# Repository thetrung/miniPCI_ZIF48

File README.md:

mini-PCI to ZIF-48P
====================
Just a simple PCB Design practice to make old mini-pcie-type-3 with single-side 62 pins to connect to socket ZIF-48 pins.

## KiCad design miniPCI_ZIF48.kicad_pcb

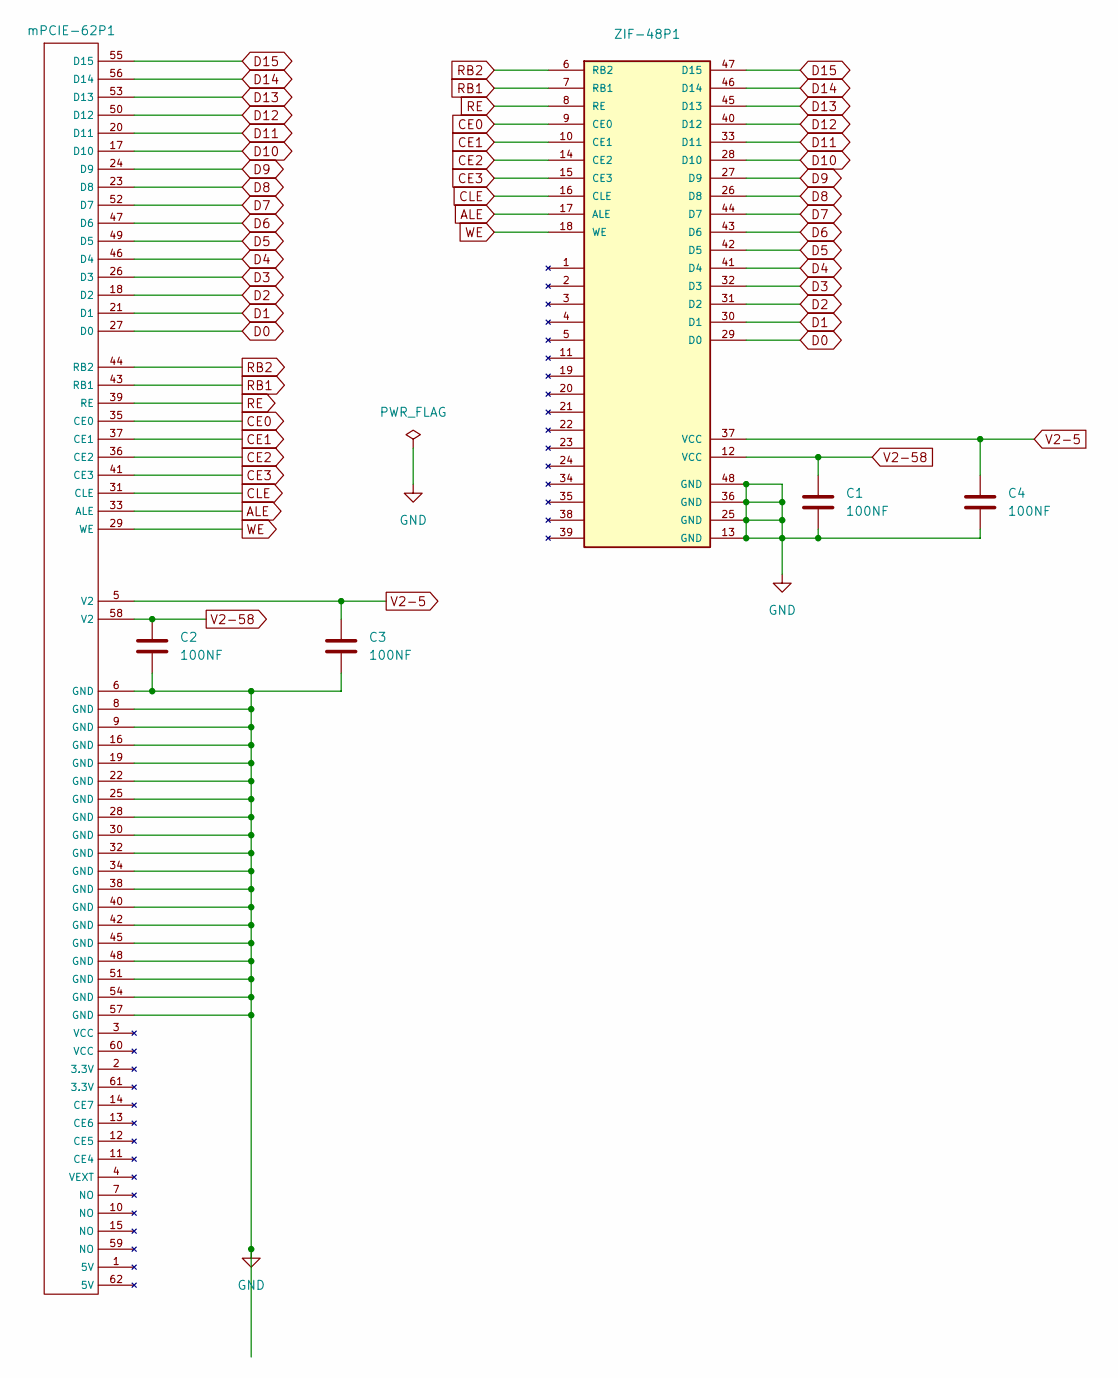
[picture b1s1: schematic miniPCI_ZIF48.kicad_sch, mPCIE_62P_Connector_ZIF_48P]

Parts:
C1, C2, C3, C4: 100NF; C_1206_3216Metric
ZIF-48P1: DIP-48_W15.24mm_Socket
mPCIE-62P1: MINIPCI_TYPE_IIIA

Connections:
ALE: ZIF-48P1.17 (ALE), mPCIE-62P1.33 (ALE)
CE0: ZIF-48P1.9 (CE0), mPCIE-62P1.35 (CE0)
CE1: ZIF-48P1.10 (CE1), mPCIE-62P1.37 (CE1)
CE2: ZIF-48P1.14 (CE2), mPCIE-62P1.36 (CE2)
CE3: ZIF-48P1.15 (CE3), mPCIE-62P1.41 (CE3)
CLE: ZIF-48P1.16 (CLE), mPCIE-62P1.31 (CLE)
D0: ZIF-48P1.29 (D0), mPCIE-62P1.27 (D0)
D1: ZIF-48P1.30 (D1), mPCIE-62P1.21 (D1)
D2: ZIF-48P1.31 (D2), mPCIE-62P1.18 (D2)
D3: ZIF-48P1.32 (D3), mPCIE-62P1.26 (D3)
D4: ZIF-48P1.41 (D4), mPCIE-62P1.46 (D4)
D5: ZIF-48P1.42 (D5), mPCIE-62P1.49 (D5)
D6: ZIF-48P1.43 (D6), mPCIE-62P1.47 (D6)
D7: ZIF-48P1.44 (D7), mPCIE-62P1.52 (D7)
D8: ZIF-48P1.26 (D8), mPCIE-62P1.23 (D8)
D9: ZIF-48P1.27 (D9), mPCIE-62P1.24 (D9)
D10: ZIF-48P1.28 (D10), mPCIE-62P1.17 (D10)
D11: ZIF-48P1.33 (D11), mPCIE-62P1.20 (D11)
D12: ZIF-48P1.40 (D12), mPCIE-62P1.50 (D12)
D13: ZIF-48P1.45 (D13), mPCIE-62P1.53 (D13)
D14: ZIF-48P1.46 (D14), mPCIE-62P1.56 (D14)
D15: ZIF-48P1.47 (D15), mPCIE-62P1.55 (D15)
GND: C1.2, C2.1, C3.1, C4.2, ZIF-48P1.13 (GND), ZIF-48P1.25 (GND), ZIF-48P1.36 (GND), ZIF-48P1.48 (GND), mPCIE-62P1.6 (GND), mPCIE-62P1.8 (GND), mPCIE-62P1.9 (GND), mPCIE-62P1.16 (GND), mPCIE-62P1.19 (GND), mPCIE-62P1.22 (GND), mPCIE-62P1.25 (GND), mPCIE-62P1.28 (GND), mPCIE-62P1.30 (GND), mPCIE-62P1.32 (GND), mPCIE-62P1.34 (GND), mPCIE-62P1.38 (GND), mPCIE-62P1.40 (GND), mPCIE-62P1.42 (GND), mPCIE-62P1.45 (GND), mPCIE-62P1.48 (GND), mPCIE-62P1.51 (GND), mPCIE-62P1.54 (GND), mPCIE-62P1.57 (GND)
RB1: ZIF-48P1.7 (RB1), mPCIE-62P1.43 (RB1)
RB2: ZIF-48P1.6 (RB2), mPCIE-62P1.44 (RB2)
RE: ZIF-48P1.8 (RE), mPCIE-62P1.39 (RE)
V2-5: C3.2, C4.1, ZIF-48P1.37 (VCC), mPCIE-62P1.5 (V2)
V2-58: C1.1, C2.2, ZIF-48P1.12 (VCC), mPCIE-62P1.58 (V2)
WE: ZIF-48P1.18 (WE), mPCIE-62P1.29 (WE)

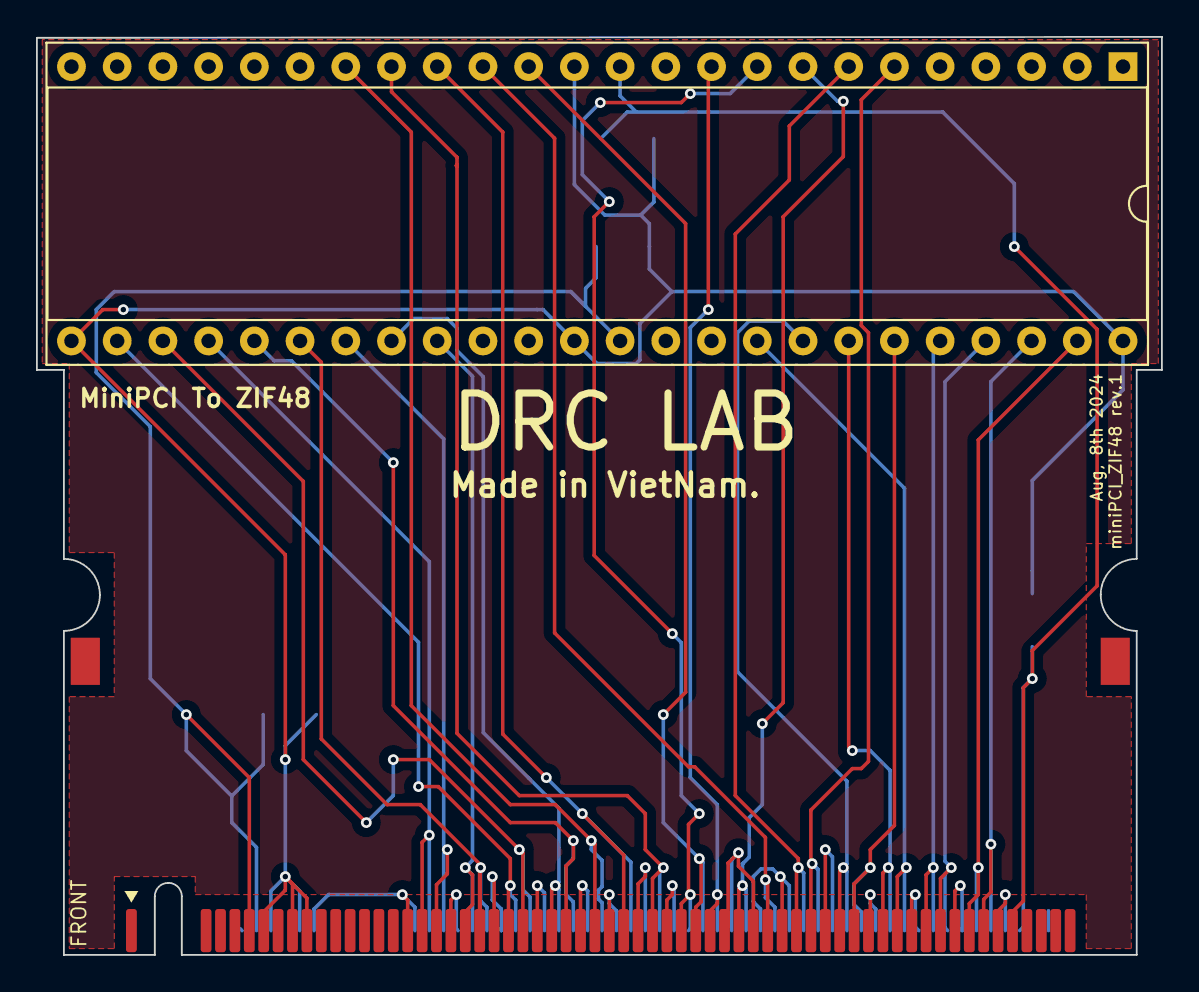
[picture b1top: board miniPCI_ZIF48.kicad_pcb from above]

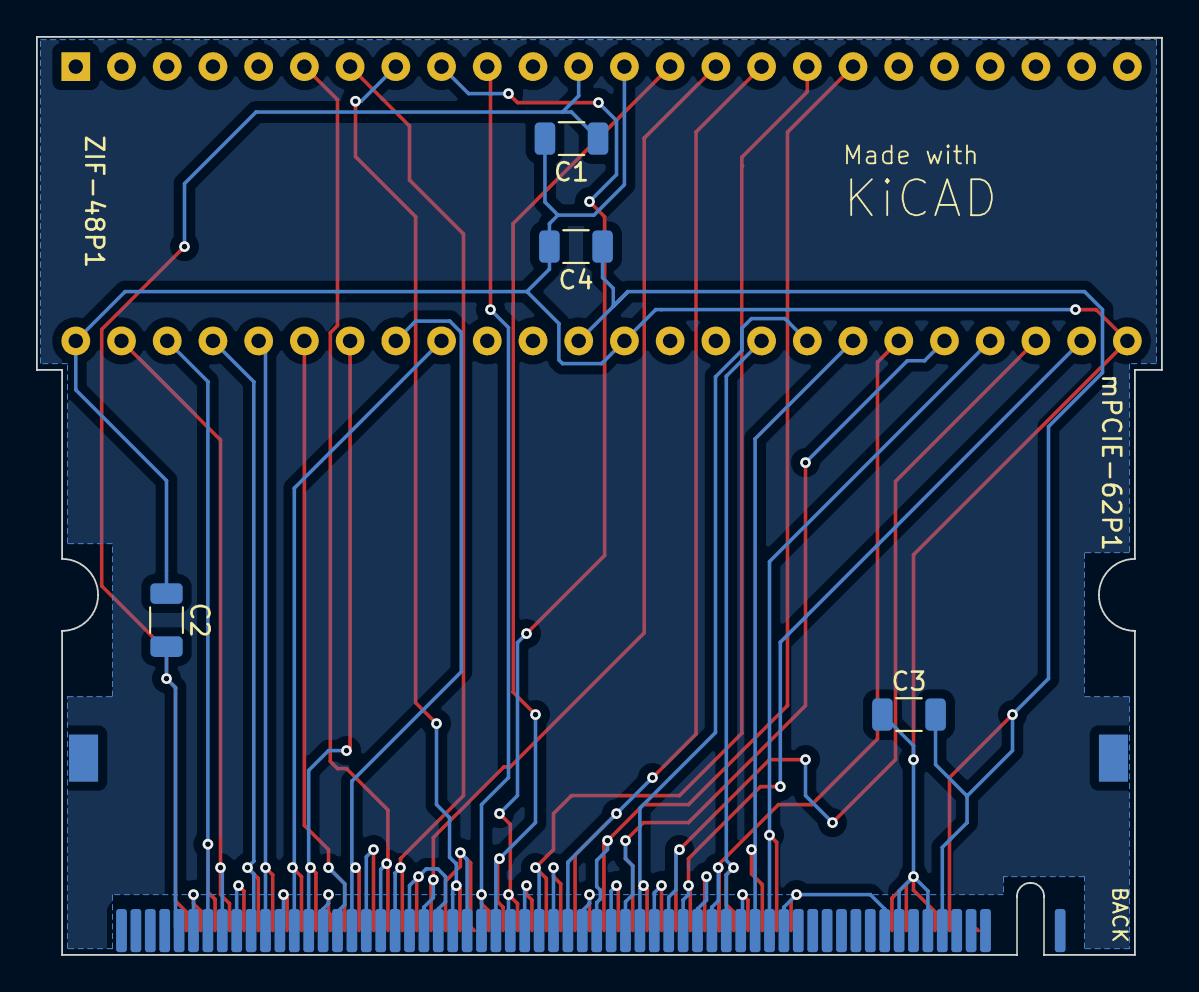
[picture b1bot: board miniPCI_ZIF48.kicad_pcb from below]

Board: 2 copper layers, 62.5 x 51.0 mm, 6 parts (4 on the bottom side), 29 nets.

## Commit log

2024-08-03 Add schematic rev 1.0
2024-08-04 rev.1 : Fix V2/VEXT powersupply, mPCI output signal labels, RB1/2 pin-swap, +RB3/4
2024-08-04 re-arrange data pins to follow NAND_Adapter + TSOP-48 arrangement
2024-08-04 Fix ZIF pinout to exactly similiar to NAND schematic
2024-08-04 remove unused pins on mPCIE
2024-08-04 pump up revision.
2024-08-04 Remove 3V3 & VCC from mPCI
2024-08-04 Remove 2 Capacitors from ZIF/VCC & connect V2->VCC directly.
2024-08-04 Fix decoupling capacitors to fit on each mPCI/ZIF closer & grounded.
2024-08-04 Pumping Rev -> 1.3
2024-08-04 data pinouts arrangement by ONFI-X16. rev 1.3 -> 1.4
2024-08-04 Fix ERC errors on buses, annotations, powerline issues
2024-08-04 add comment about PWR_FLAG->GND
2024-08-04 Add footprints for ZIF-48 & mini-PCI-Type-III
2024-08-05 re-mapping mPCIe -> same 62 pins on both side.
2024-08-07 Passed all DRCs/PCB_Editor
2024-08-07 Add Texts & Design
2024-08-08 Silkscreen design & finish Gerber.
2024-08-10 Refine into only 2-layers design, both copper filled.
